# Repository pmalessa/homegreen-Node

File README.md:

# HomeGreen - self watering system
## Description
A self watering system for outdoor plants. This project contains the hardware and software files to completely build a HomeGreen node on your own.

The system is based on an inexpensive node, which is able to control up to 3 pumps and can be powered by nearly any conventional powerbank. It has a basic user interface using a 6-Digit 7-Segment Display combined with 4 touch buttons. As a pump, you could either use a 4-6V DC pump or a 5V relay to control a higher voltage pump. The node is designed to be water resistant and can be easily mounted using embedded magnets or a 3D printed holder.

## Repository structure
This repo contains everything you need to build a homegreen node on your own:

- hardware: The EAGLE PCB and GERBER files, BOM and models and dimensions for the case
- firmware: The firmware for the microcontroller (attiny88) on the node

## Hardware
The HomeGreen node PCB is designed to be enclosed in a 25mm diameter transparent pipe to be water resistant. The touch buttons can be used through the pipe without the need to open the case. The 2 ends need plastic caps, which could be easily 3D printed. one needs to be fully closed, while the other one needs to have an opening the for USB-A connector of the pump as well as the micro USB connector of the powerbank.

## Firmware
The firmware is written in low-level C++ and uses the PlatformIO framework. It is designed to run as energy efficient as possible to be able to run on a powerbank for a long time.

## Detailed description
The HomeGreen node contains the following main components:
- an attiny88 microcontroller as main controller
- a sophisticated power management circuit to be able to sleep and wake up the connected powerbank regularly
- a 6-Digit 7-Segment Display with its controller as user interface
- a 4-Channel touch button controller as user interface
- an I2C temperature sensor to measure the temperature of the environment
- a current limiter, step-up converter and a current measurement circuit to adjust and monitor the output power for the pump
- the ability to control up to 3 pumps sequentially using an additional HomeGreen Pump Hub

### Power management
The main issue of supplying your gadgets using a powerbank is the fact, that nearly all powerbanks shut off after a certain time of inactivity. As the sleep current draw of the HomeGreen node is substantially lower than any charge current the powerbank is designed for, it treats it as inactive and shuts off eventually. 

This led to the necessity to have a supercapacitor as an additional short-time energy storage onboard to be able to power the controller while in sleep and only wake the powerbank once the supercap is drained or it is time to enable the pump.

Additionally, each powerbank is behaving differently when it comes to the sleep and wake behavior. Some powerbanks wake up immediately once you connect the capacitive load of the supercap, while others require an additional substantial resistive load to enable its regulators. Strangely, some powerbanks even change their polarity and apply -2.5V to their output!

To support most of the available powerbanks on the market 2 MOSFETS back to back, combined with a charge pump and an additional controllable resistive load was necessary. Even with that, some powerbanks do not work reliably and should be avoided. A list of tested powerbanks will be added.

### User Interface
The HomeGreen Node consists of a 6-Digit 7-Segment display as well as 4 touch buttons to view its status and adjust all parameters to your needs. The HomeGreen Node can be used to control up to 3 pumps using an additional HomeGreen Pump Hub. Once connected, the user interface switches to the ability to adjust timing of each pump separately. However, if no Pump Hub is connected, it is simplyfied to control just one pump.

#### Sleep State
In its default sleep state, the 7-Segment Display is turned off and only the 2 Status LEDs are displaying its state. 
- If it blinks green once every 8 seconds, everything is fine. 
- If it blinks green twice and in a faster interval, it charges its supercap. This happens every 5-15mins. 
- If it blinks red, an error occured and the Node should be checked by waking it to get more details.
- If it is time to water the plants, it will wake itself and continue with the Pump State.
- To wake the Node, just touch one of its touch buttons. It will then try to wake the powerbank and will turn on its Display, once successful. It may take multiple tries sometimes depending on the model of powerbank. It then moves into Info State. If an error occured, it will switch into Error State after wake up before going to Info State.

#### Info State
In the info state, you see the set interval and duration of the pump cycle as well as the time left till the next pump cycle at one glance. If a Pump Hub is connected, you can switch between the config for each pump with a short press of the SET button.
- If no button is pressed, it shuts off and switches back to Sleep State after some time.
- To adjust the interval or duration of the pump cycle, long press the SET button and wait for the display to fade out and in. It now switched into Config State.
- To start a manual pump cycle, just long press the MANUAL button. It then switches into Pump State.

#### Config State
In the Config State, you can adjust the interval and duration of the pump cycle. The currently selected parameter is displayed by blinking its number.
- To increase the parameter, short press or hold the + button.
- To decrease the parameter, short press of hold the - button.
- To switch the selected parameter, short press the SET button.
- To save the newly configured parameters, long press the SET button. It switches to Info State then.
- If no button have been pressed for a longer period, changes are discarded and it switches to Info State.
- To get more advanced information and configuration options, long press the MANUAL button to switch to Advanced State.

#### Pump State
Once the pump interval elapsed or a manual pump cycle has been started, the Node switches into Pump State. In Pump State, an animation is displayed as well as the time left to pump in the current cycle. If a Pump Hub is connected, it will additionally display which pump is currently enabled.
- To increase the current pump cycle by 1 minute, short press the + button.
- To decrease the current pump cycle by 1 minute, short press the - button.
- To manually switch to the next pump, short press the SET button.
- To stop the current pump cycle, long press the MANUAL button.
- Once the pump duration of all pumps elapsed, the Node will switch to Info State to shortly display its current parameters, and after some time of inactivity it switches back to Sleep State.

#### Error State
If an error ocurred, the red led blinks to signal that something went wrong. To check for details, wake the node and it will switch to this state.
The following errors are possible:
- PB_ERR: Powerbank-Error - The node was not possible to wake the powerbank at its last wake up by a pump cycle or a user action. Check the charge state or cabling of the powerbank. Maybe that model is incompatible with the Node, check the list of tested powerbanks for hints.
- P1_ERR/P2_ERR/P3_ERR: Pump1/2/3-Error - There is an issue with the mentioned pump, the current draw had an anomaly. Maybe the cable is broken, the water tank is empty or the pump is clogged.
- EP_ERR: EEPROM-Error - There is an issue with the save state of the configuration. This rarely happens, but sometimes the config can get corrupted by battery drain. The config will be reset to default state and it has to be reconfigured.

The following interactions are possible:
- To clear the current error, short press any button.
- To ignore the current error permanently (until the next reset to defaults), long press the MANUAL button.

#### Advanced State
The Advanced State contains additional information and configuration options to move through.
The following informations are displayed:
- The build date of the firmware
- The build version of the firmware
- The current runtime in hours
- The total runtime in hours

The following interactions are possible:
- To move to the next information, short press the SET button
- To leave the Advanced State back to Info State, long press the SET button
- To reset all configurations to its default state, long press the MANUAL button. It then switches back to Info State.

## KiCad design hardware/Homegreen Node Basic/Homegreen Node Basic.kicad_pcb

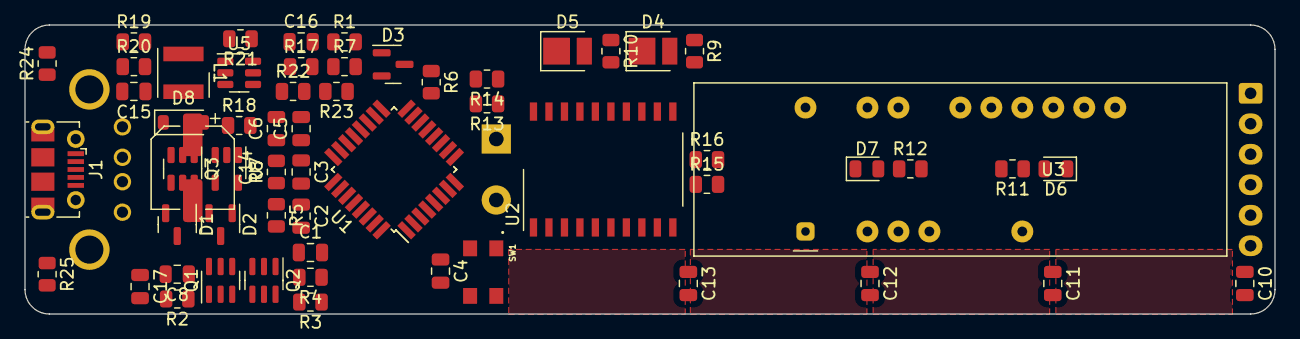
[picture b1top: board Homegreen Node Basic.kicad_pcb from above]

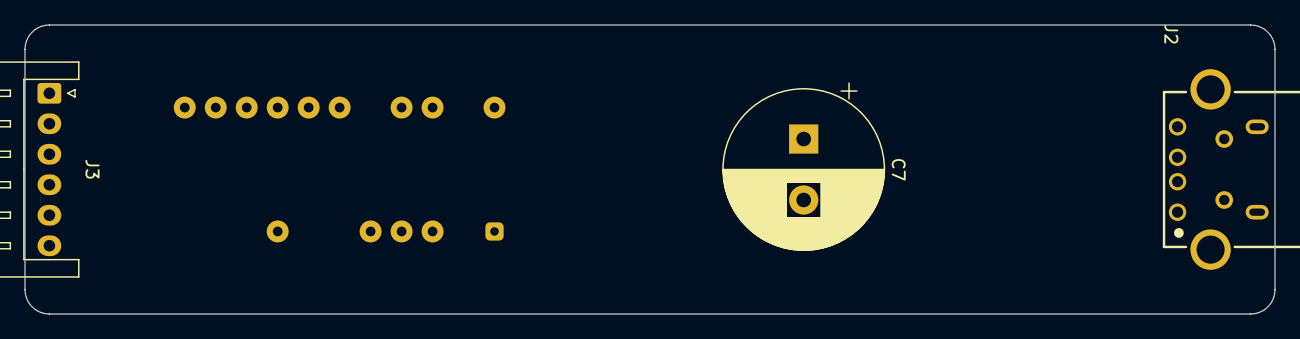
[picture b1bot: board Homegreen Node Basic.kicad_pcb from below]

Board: 2 copper layers, 102.5 x 23.7 mm, 62 parts (3 on the bottom side), 55 nets, no tracks yet.

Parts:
C1, C2, C3, C4, C5, C6, C8: 100n; C_0805_2012Metric
C7: 0.33F; CP_Radial_D13.0mm_P5.00mm
C10, C11, C12, C13: 5p; C_0805_2012Metric
C14: 330u; CP_Elec_6.3x5.8
C15, C16, C17: 10u; C_0805_2012Metric
D1, D2, D3: BAT54S; SOT-23
D4: gr; LED_PLCC_2835
D5: red; LED_PLCC_2835
D6, D7: wh; LED_0805_2012Metric
D8: DSS24; D_SOD-123
J1: USB_B_Micro; USB_Micro-B_Molex-105017-0001
J2: USB_A; Wuerth_61400416021
J3: Conn_01x06_Pin; JST_XH_S6B-XH-A_1x06_P2.50mm_Horizontal
L1: 2.2u; L_Wurth_WE-LQSH-4020
Q1, Q2: BC817DPN; SC-74-6_1.5x2.9mm_P0.95mm
Q3: WST2011; SOT-23-6
R1, R3, R7, R8, R15, R16, R17, R20, R24, R25: 100k; R_0805_2012Metric
R2, R6: 47; R_0805_2012Metric
R4, R11, R12, R13, R14, R21: 1k; R_0805_2012Metric
R5: 1M; R_0805_2012Metric
R9, R10: 3k; R_0805_2012Metric
R18: 4k7; R_0805_2012Metric
R19, R22, R23: 10k; R_0805_2012Metric
SW1: SW_Push; SW_DHT-4235A
U1: ATmega328PB; TQFP-32_7x7mm_P0.8mm
U2: TM1637; SO-20_12.8x7.5mm_P1.27mm
U3: FJ3661BH
U5: MT3608; SOT-23-6
U7: MT9700; SOT-23-5

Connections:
/BTN_LED: R11.2, R12.2, U1.23 (PC0)
/EN_CLK: C1.2, U1.15 (PB3)
/EN_LOAD: Q1.2 (B1), R4.2
/EN_PUMP: R17.1, U5.4 (EN), U7.4 (EN)
/LED_OK: R9.2, U1.16 (PB4)
/MISO: J3.1, U1.7 (XTAL1/PB6)
/MOSI: J3.4, U1.17 (PB5)
/PUMP_VOL: R23.1, U1.25 (PC2)
/RESET: C3.2, C4.1, J3.5, R8.1, SW1.1, U1.29 (~RESET/PC6)
/SCK: J3.3, U1.8 (XTAL2/PB7)
/TM_CLK: R13.2, R15.1
/TM_DIO: R14.2, R16.1
/USB1: J2.2 (D-), R24.1, U1.26 (PC3)
/USB2: J2.3 (D+), R25.1, U1.14 (PB2)
/User Interface/DIG1: U2.15 (GRID1), U3.22 (CA1)
/User Interface/DIG2: U2.14 (GRID2), U3.3 (CA2)
/User Interface/DIG3: U2.13 (GRID3), U3.4 (CA3)
/User Interface/DIG4: U2.12 (GRID4), U3.16 (CA4)
/User Interface/DIG5: U2.11 (GRID5), U3.13 (CA5)
/User Interface/DIG6: U2.10 (GRID6), U3.12 (CA6)
/~EN_PB: D2.1 (A), U1.27 (PC4)
BAT_PWR: C3.1, C5.1, C6.1, C7.1, J3.2, R6.2, R8.2, U1.4 (VCC), U1.18 (AVCC), U1.20 (AREF)
GND: C2.2, C4.2, C5.2, C6.2, C7.2, C8.2, C10.2, C11.2, C12.2, C13.2, C14.2, C15.2, C16.2, C17.2, D4.1 (K), D5.1 (K), D6.1 (K), D7.1 (K), J1.5 (GND), J1.6 (Shield), J2.5 (Shield), J3.6, R2.2, R5.2, R7.1, R17.2, R18.2, R21.2, R24.2, R25.2, SW1.2, U1.5 (GND), U1.21 (GND), U2.1 (GND), U5.2 (GND), U7.2 (GND)
unnamed: C16.1, R22.1, R23.2
unnamed: D1.1 (A), Q2.1 (E1), R3.1
unnamed: D1.3 (COM), J1.1 (VBUS), Q3.6 (D)
unnamed: D1.2 (K), Q1.5 (B2), Q1.6 (C1)
unnamed: C1.1, D2.3 (COM)
unnamed: C2.1, D2.2 (K), Q3.1 (G), Q3.3 (G), R5.1
unnamed: D3.3 (COM), R6.1
unnamed: D4.2 (A), R9.1
unnamed: D5.2 (A), R10.1
unnamed: D6.2 (A), R11.1
unnamed: D7.2 (A), R12.1
unnamed: D8.2 (A), L1.2, U5.1 (SW)
unnamed: C14.1, C17.1, D8.1 (K), J2.1 (VBUS), R19.1, R20.1
unnamed: Q1.1 (E1), Q2.6 (C1), R2.1
unnamed: Q1.3 (C2), Q2.2 (B1), R3.2
unnamed: Q1.4 (E2), R4.1
unnamed: Q3.2 (S), Q3.5 (S)
unnamed: R1.1, R7.2
unnamed: R13.1, U2.18 (CLK)
unnamed: R14.1, U2.17 (DIO)
unnamed: U2.2 (SEG1/KS1), U3.15 (A)
unnamed: U2.3 (SEG2/KS2), U3.20 (B)
unnamed: U2.4 (SEG3/KS3), U3.19 (C)
unnamed: U2.5 (SEG4/KS4), U3.5 (D)
unnamed: U2.6 (SEG5/KS5), U3.1 (E)
unnamed: U2.7 (SEG6/KS6), U3.14 (F)
unnamed: U2.8 (SEG7/KS7), U3.17 (G)
unnamed: U2.9 (SEG8/KS8), U3.8 (DP)
unnamed: R19.2, R20.2, R21.1, R22.2, U5.3 (FB)
unnamed: C15.1, L1.1, U5.5 (IN), U7.1 (VOUT)
unnamed: R18.1, U7.3 (SET)
USB_PWR: C8.1, D3.1 (A), Q3.4 (D), R1.2, R15.2, R16.2, U2.16 (VDD), U7.5 (VIN)

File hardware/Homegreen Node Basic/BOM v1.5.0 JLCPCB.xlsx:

Comment | Designator | Footprint | JLCPCB Part #（optional）
ATmega328PB | U1 | TQFP-32_7x7mm_P0.8mm
USB_A | J2 | Wuerth_61400416021
MT3608 | U5 | SOT-23-6
MT9700 | U7 | SOT-23-5
wh | D6,D7 | LED_0805_2012Metric
WST2011 | Q3 | SOT-23-6
2.2u | L1 | L_Wurth_WE-LQSH-4020
1k | R12,R11,R14,R21,R13,R4 | R_0805_2012Metric
red | D5 | LED_PLCC_2835
100k | R17,R7,R24,R15,R25,R1,R20,R8,R3,R16 | R_0805_2012Metric
BAT54S | D1,D2,D3 | SOT-23
DSS24 | D8 | D_SOD-123
47 | R6,R2 | R_0805_2012Metric
TM1637 | U2 | SO-20_12.8x7.5mm_P1.27mm
FJ3661BH | U3 | FJ3661BH
gr | D4 | LED_PLCC_2835
BC817DPN | Q2,Q1 | SC-74-6_1.5x2.9mm_P0.95mm
100n | C5,C2,C1,C4,C8,C3,C6 | C_0805_2012Metric
5p | C13,C11,C12,C10 | C_0805_2012Metric
3k | R10,R9 | R_0805_2012Metric
Conn_01x06_Pin | J3 | JST_XH_S6B-XH-A_1x06_P2.50mm_Horizontal
1M | R5 | R_0805_2012Metric
10u | C17,C16,C15 | C_0805_2012Metric
10k | R19,R23,R22 | R_0805_2012Metric
USB_B_Micro | J1 | USB_Micro-B_Molex-105017-0001
4k7 | R18 | R_0805_2012Metric
0.33F | C7 | CP_Radial_D13.0mm_P5.00mm
SW_Push | SW1 | SW_DHT-4235A
330u | C14 | CP_Elec_6.3x5.8

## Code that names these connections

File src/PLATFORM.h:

/*
 * PLATFORM.h
 *
 *  Created on: 25.01.2019
 *      Author: pmale
 */

#ifndef PLATFORM_H_
#define PLATFORM_H_

#include <avr/io.h>
#include <util/delay.h>
#include <avr/interrupt.h>
#include <avr/pgmspace.h>
#include <avr/sleep.h>
#include <stdlib.h>

#define BUILD_DAY 05
#define BUILD_MONTH 07
#define BUILD_YEAR 22
#define BUILD_VERSION_MAJOR 1
#define BUILD_VERSION_MINOR 4
#define BUILD_VERSION_PATCH 7

#ifdef HG_BASIC_HW_1_4_4

#define FEATURE_PUMP_STRENGTH
#define FEATURE_PUMP_SENSOR

#define CHK_5V_DDR DDRA
#define CHK_5V_PORT PORTA
#define CHK_5V_PIN PA0
#define CHK_5V_PINREG PINA

#define PUMP_DDR DDRA
#define PUMP_PORT PORTA
#define PUMP_PIN PA1

#define TOUCH_PWR_DDR DDRA
#define TOUCH_PWR_PORT PORTA
#define TOUCH_PWR_PIN PA2

#define USB_OUT_P_DDR DDRB
#define USB_OUT_P_PORT PORTB
#define USB_OUT_P_PIN PB0
#define USB_OUT_P_PINREG PINB

#define EN_CLK_DDR DDRB
#define EN_CLK_PORT PORTB
#define EN_CLK_PIN PB1

#define LED_GREEN_DDR DDRB
#define LED_GREEN_PORT PORTB
#define LED_GREEN_PIN PB2

#define LED_BTN_DDR DDRB
#define LED_BTN_PORT PORTB
#define LED_BTN_PIN PB7

#define PUMP_VOL_DDR DDRC
#define PUMP_VOL_PORT PORTC
#define PUMP_VOL_PIN PC0

#define USB_OUT_M_DDR DDRC
#define USB_OUT_M_PORT PORTC
#define USB_OUT_M_PIN PC1
#define USB_OUT_M_PINREG PINC

#define EN_PB_DDR DDRC
#define EN_PB_PORT PORTC
#define EN_PB_PIN PC2

#define PUMP_CUR_DDR DDRC
#define PUMP_CUR_PORT PORTC
#define PUMP_CUR_PIN PC3
#define PUMP_CUR_PINREG PINC

#define I2C_SDA_DDR DDRC
#define I2C_SDA_PORT PORTC
#define I2C_SDA_PIN PC4

#define I2C_SCL_DDR DDRC
#define I2C_SCL_PORT PORTC
#define I2C_SCL_PIN PC5

#define EN_LOAD_DDR DDRD
#define EN_LOAD_PORT PORTD
#define EN_LOAD_PIN PD0

#define TM_OUT          PORTD
#define TM_IN           PIND
#define TM_DDR          DDRD
#define TM_BIT_DAT      _BV(PD5)
#define TM_BIT_CLK      _BV(PD6)

#define LED_RED_DDR DDRD
#define LED_RED_PORT PORTD
#define LED_RED_PIN PD7

#elif defined(HG_BASIC_HW_1_4_3)
#define DEBUG1_DDR DDRC
#define DEBUG1_PORT PORTC
#define DEBUG1_PIN PC0

#define EN_PB_DDR DDRC
#define EN_PB_PORT PORTC
#define EN_PB_PIN PC2

#define EN_LOAD_DDR DDRC
#define EN_LOAD_PORT PORTC
#define EN_LOAD_PIN PC3

#define CHK_5V_DDR DDRA
#define CHK_5V_PORT PORTA
#define CHK_5V_PIN PA0
#define CHK_5V_PINREG PINA

#define TOUCH_PWR_DDR DDRA
#define TOUCH_PWR_PORT PORTA
#define TOUCH_PWR_PIN PA2

#define I2C_SCL_DDR DDRC
#define I2C_SCL_PORT PORTC
#define I2C_SCL_PIN PC5

#define I2C_SDA_DDR DDRC
#define I2C_SDA_PORT PORTC
#define I2C_SDA_PIN PC4

#define EN_CLK_DDR DDRB
#define EN_CLK_PORT PORTB
#define EN_CLK_PIN PB1

#define LED_RED_DDR DDRD
#define LED_RED_PORT PORTD
#define LED_RED_PIN PD7

#define LED_GREEN_DDR DDRB
#define LED_GREEN_PORT PORTB
#define LED_GREEN_PIN PB2

#define LED_BTN_DDR DDRB
#define LED_BTN_PORT PORTB
#define LED_BTN_PIN PB7

#define PUMP_DDR DDRA
#define PUMP_PORT PORTA
#define PUMP_PIN PA1

#define USB_OUT_M_DDR DDRC
#define USB_OUT_M_PORT PORTC
#define USB_OUT_M_PIN PC1
#define USB_OUT_M_PINREG PINC

#define USB_OUT_P_DDR DDRB
#define USB_OUT_P_PORT PORTB
#define USB_OUT_P_PIN PB0
#define USB_OUT_P_PINREG PINB

#define USB_IN_SW_DDR DDRC
#define USB_IN_SW_PORT PORTC
#define USB_IN_SW_PIN PC7

#define TM_OUT          PORTD
#define TM_IN           PIND
#define TM_DDR          DDRD
#define TM_BIT_CLK      _BV(PD6)
#define TM_BIT_DAT      _BV(PD5)
#endif

//#define SLEEP_INTERVAL_S 4	//4000ms = 4s
#define DISPLAY_TIMEOUT_S 10 //5sec

#define true 1
#define false 0

typedef struct{
	uint16_t u16interval;
	uint16_t u16duration;
	uint16_t countdown;
}config_t;

typedef enum{
	DIGIT_INTERVAL,
	DIGIT_DURATION,
	DIGIT_COUNTDOWN,
#ifdef FEATURE_PUMP_STRENGTH
	DIGIT_PUMP_STRENGTH,
#endif
}digit_t;

#define UNUSED(x) (void)(x)

/* Macros to access bytes within words and words within longs */
#define LOW_BYTE(x)     ((uint8_t)((x)&0xFF))
#define HIGH_BYTE(x)    ((uint8_t)(((x)>>8)&0xFF))
#define LOW_WORD(x)     ((uint16_t)((x)&0xFFFF))
#define HIGH_WORD(x)    ((uint16_t)(((x)>>16)&0xFFFF))

#endif /* PLATFORM_H_ */

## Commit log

2019-03-31 uploading current state
2019-03-31 gitignore
2019-03-31 last version built for t841
2019-03-31 add release compile
2019-03-31 adapted pin names
2019-04-01 port of Pin definitions done, compiles without warnings
2019-04-01 no remap necessary
2019-04-01 marking possible bug positions
2019-04-04 bug fixed, removed markings
2019-04-04 New Release
2019-04-04 removing software based I2C Master
2019-04-04 using Atmels own twi master library for t88
2019-04-04 compiles, needs test code now
2019-04-05 first test code
2019-04-05 cleanup done, saved a few kb
2019-04-10 correct button definition, + and - swapped working buzzer, but needs a diode to not destroy the pcb
2019-04-10 adding current and setup temp to DATA adding duration adjustment implementation
2019-04-22 enable PWR_IN
2019-04-22 update Build number this release is on the first 4 pcbs sent to HQ
2019-04-22 update binary
2019-04-22 set countdown value to normal hours
2019-04-29 adding boot animation fixing PowerInput switch from Powerbank to battery, reset pin was the issue
2019-05-18 display reset flag for debugging
2019-05-18 buzzer tested
2019-05-19 using peter fleury i2c library
2019-05-19 remove test code
2019-06-26 moved files removed temp sensor from code, as it causes system brick
2019-06-26 update...
2019-06-26 getting Release ready
2019-06-26 fixing parasitic power of 7segment ic over data line
2019-06-26 adding: disconnect PB while active -> go to sleep
2019-06-26 implemented powerState such that it runs independently removed powerChange callback
2019-06-26 implemented buzzer using circular buffer. This way the tones will now be played without blocking not completely bugfree yet. Plays an annoying 4s tone sometimes
2019-06-27 adding pump test and sig pin checking if power lost while pumping and goto sleep tweaking buzzer
2019-06-28 using Frequency Lookup Table instead of division inside interrupt routine to mitigate performance issues Adding a pump disable once power is lost while pumping
2019-06-28 changing ADC from onDemand to Free Running mode Implemented a ringBuffer to remove ADC measurement spikes
2019-06-28 adding a ADC Stable flag which signalizes if 10 measurements are completed after initialization
2019-08-17 disable heartbeat fix adc_stable
2019-08-18 working on v1.3
2019-08-18 implementing capLow Recharge implementing PB Empty Alarm
2019-08-20 removed buzzer display timeout to 5s load counter to 2s
2019-09-07 adding a wakeUpState
2019-09-07 Use Buzzer pin as sleep debug pin. LOW if in sleep, HIGH if active
2019-09-08 fixing
2019-11-15 add charge cap functionality removed pump power lost feature
2020-01-31 ported ide to vscode platformio removed Release.zip, using Bitbucket Releases from now on
2020-02-28 first step
2020-03-01 finished basic port, compiles.
2020-03-01 optimizing state machine, adding comments
2020-03-08 cleanup of power
2020-03-14 buttons working, power detection still patched out
2020-03-16 fixed hello animation fixed pump counter using 5V Pin for isPowerConnected -> works great! after reset -> blink blue if no PB connected -> blink green if PB connected
2020-03-21 Adding MAN Long Press in Config mode for resetting data. Using 5V Pin for Power detection
2020-03-22 hub implementation
2020-04-07 some updates
2020-04-11 pull down i2c and tm pins in sleep to keep 5V low use ADC for cap measurement instead of BOD -> disable by fuses again
2020-04-12 implementing Clock Output for voltage doubler
2020-04-12 switched back to 1MHz
2020-04-23 fixing LED blink
2020-04-30 testing of new LoadCircuit
2020-05-09 tweaking timings
2020-05-09 Adding Info Screen, Moving Reset to Info Screen
2020-05-09 fixing BlinkDelay
2020-05-10 reimplemented temp
2020-05-10 Fixed Temp Display Fixed Blinking Added totalRuntime, saves every day Fixed HubDisplay Removed Pump Decrement below 1min
2020-05-11 renamed Signal moved all Pin Definitions to PLATFORM.h
2020-05-14 Disable Brownout Remove Display Charge Animation, replacing with LED Fade replace all delays with Short Sleeps Add Solar Signal 1sec before wakeup of powerbank Increase LowVoltage to 3V Fixing Temp S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
2020-05-14 Release 1.3.4: Optimized energy consumption and UX
2020-05-20 - added status bits and ignore status bits to data structure - added error state to display last error - removed boot animation, directly to sleep on powerup - added separate charge state, with no UI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
    - changed button threshold to 50ms
    - code cleanup
2020-05-20 - added ignoreFunctionality - added customCountdown Function for delayed PBTest - fixed glitchy Display Wake - added PBError Functionality - Pump Test not working on current HW, removed
2020-05-20 new Release v1.4.0
2020-06-22 Changed Sleep Timer Source from WDT to Timer0, 250ms Timer Timer1 now responsible for both Clock Source and active 1ms Clock Included CRC Protection for EEPROM Corruption Detection Implemented EEPROM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
2020-09-09 new default data
2020-09-12 applied changes for new hardware. Removed Pump Check. Added multiple LEDs
2020-09-12 fixed double wakeup bug renamed to SHOW_ERROR moved decCountdown out of ISR
2020-09-12 fixed timer sleep not feeding watchdog disabling solar charger for now
2020-09-14 fixed runtime Timer added savePending to EEPROM to delay save to higher voltage state fixed EEPROM CRC added redgreen LED Blink
2021-08-06 - version 1.4.6, massively improved EEPROM saving
2022-01-17 - lets build a map - initial: 8140Bytes Flash, 179Bytes RAM - now: 8120 Flash by saving an if
2022-07-01 - simplified display code
2022-07-06 - changed pin definitions for hw1.4.4 - added multiple environments to build multiple targets
2022-07-08 - adding strength data
2022-07-08 - removing temp sensor
2022-07-08 - Feature Pump Strength done
2023-02-26 cleanup and add readme
2023-02-27 typos
2024-04-19 - fix platformio config - add pump oscillating feature
2024-04-19 update BRD and BOM
2024-04-19 add kicad files
2024-05-02 - starting with port to atmega328p
2024-05-05 - switched back to 1.8V BOD, necessary for Solar PB - increased blink Delay while sleep to 8s and charging to 4s - added charging dependency on PB Fill State - modified wake pattern - increased Cap c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
2024-05-07 - simplify wakeup code - added 2.5s delay beofre starting to pump - added pump start animation
2024-06-02 enable Blinking on Display Screen
2024-06-08 update PCB to 1-sided for price estimation
2024-06-12 - added 5V Pin debouncing
2024-07-10 add clearing of PB Error, when the last pump cycle was successful
2025-04-19 Kicad update
